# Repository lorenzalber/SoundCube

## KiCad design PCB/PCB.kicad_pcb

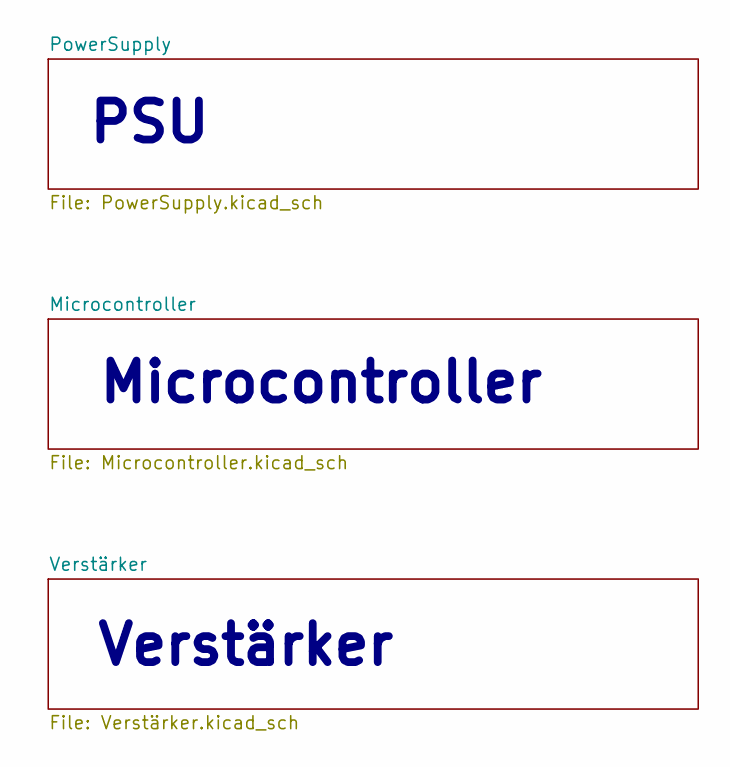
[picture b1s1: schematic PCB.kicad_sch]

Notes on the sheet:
Microcontroller
PSU
Verstärker

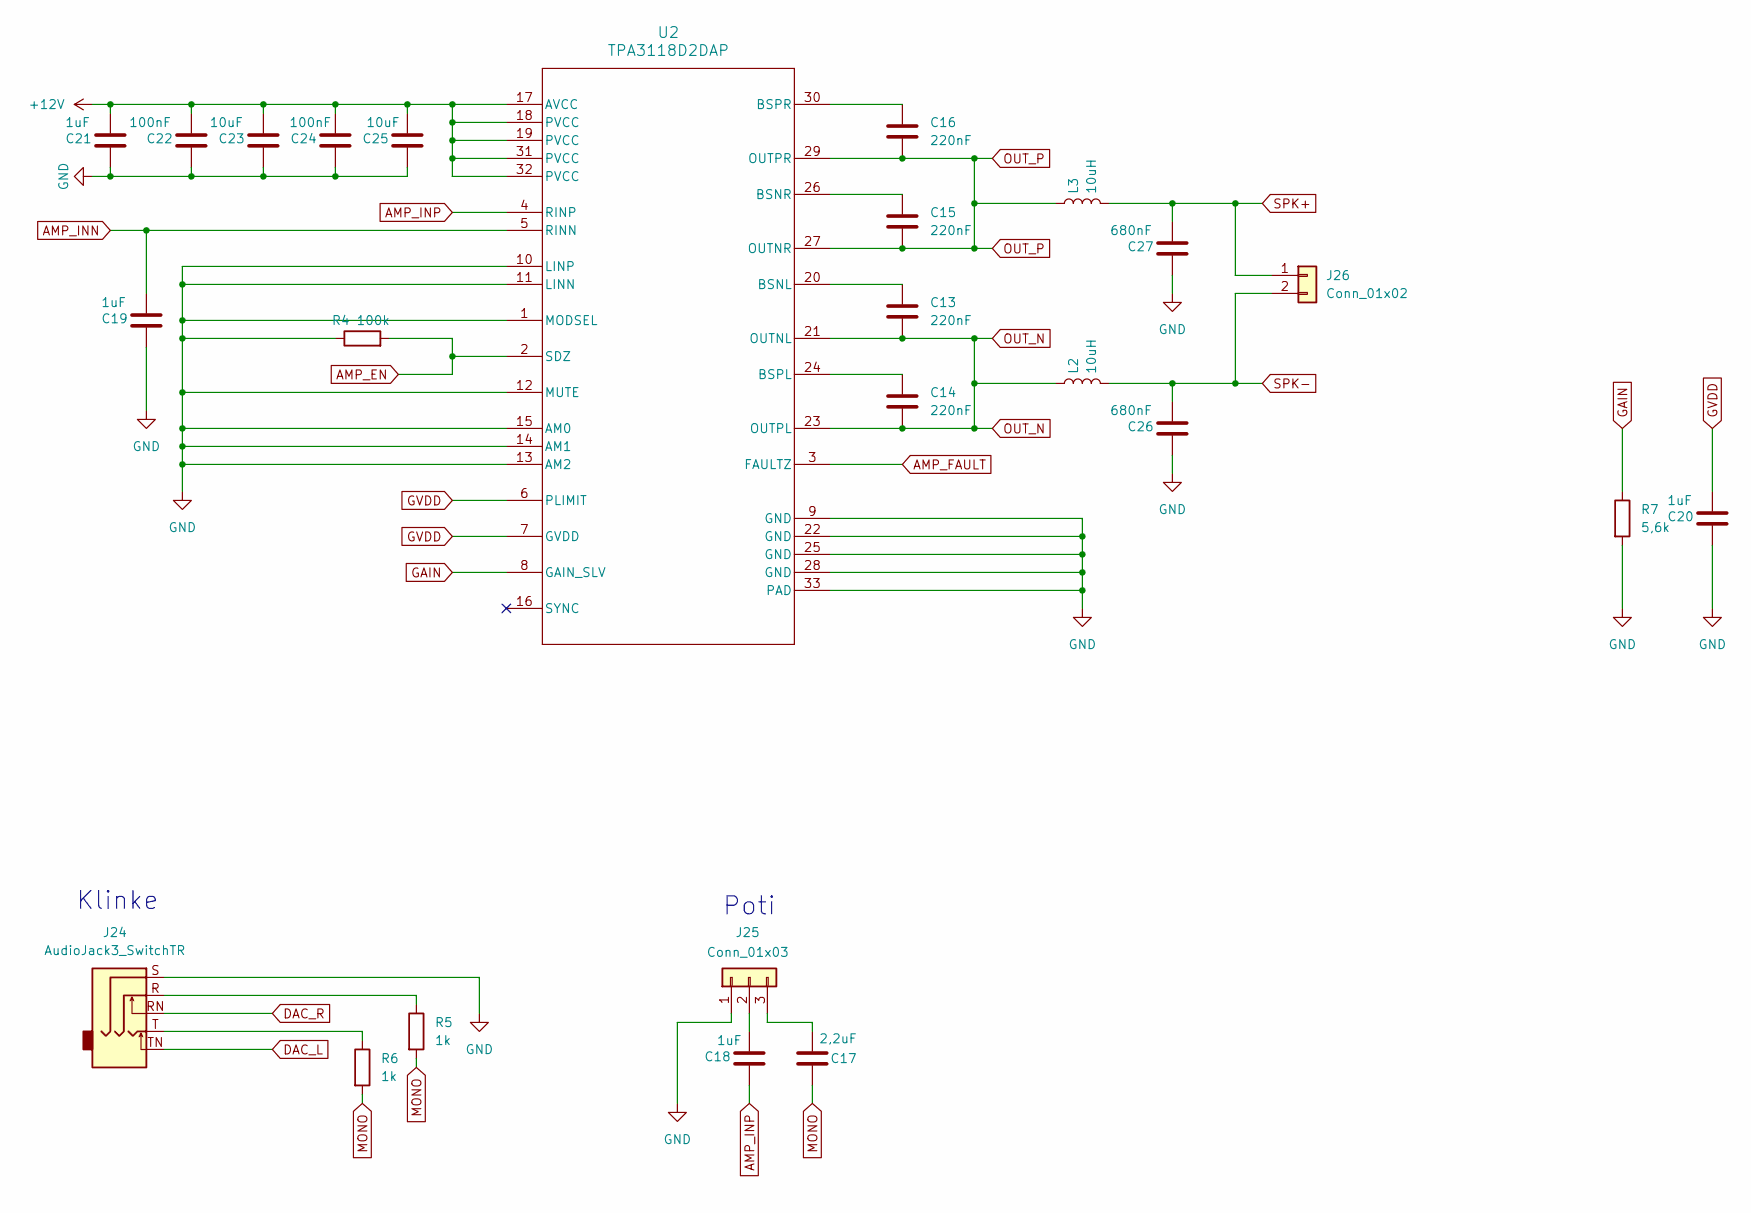
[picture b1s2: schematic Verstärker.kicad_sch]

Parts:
C13, C14, C15, C16: 220nF; C_0805_2012Metric
C17: 2,2uF; C_0805_2012Metric
C18, C19, C20, C21: 1uF; C_0805_2012Metric
C22, C24: 100nF; C_0805_2012Metric
C23, C25: 10uF; C_0805_2012Metric
C26, C27: 680nF; C_Rect_L7.2mm_W5.5mm_P5.00mm_FKS2_FKP2_MKS2_MKP2
J24: AudioJack3_SwitchTR; Jack_3.5mm_CUI_SJ1-3535NG_Horizontal
J25: Conn_01x03; SolderWire-1sqmm_1x03_P5.4mm_D1.4mm_OD2.7mm
J26: Conn_01x02; SolderWire-1sqmm_1x02_P5.4mm_D1.4mm_OD2.7mm
L2, L3: 10uH; L_Bourns_SRR1260
R4: 100k; R_0805_2012Metric
R5, R6: 1k; R_0805_2012Metric
R7: 5,6k; R_0805_2012Metric
U2: TPA3118D2DAP; DAP0032A_M

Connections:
+12V: C21.2, C22.2, C23.2, C24.2, C25.2, U2.17 (AVCC), U2.18 (PVCC), U2.19 (PVCC), U2.31 (PVCC), U2.32 (PVCC); also elsewhere on the board
AMP_EN: R4.2, U2.2 (SDZ); also elsewhere on the board
AMP_FAULT: U2.3 (FAULTZ); also elsewhere on the board
AMP_INN: C19.2, U2.5 (RINN)
AMP_INP: C18.1, U2.4 (RINP)
DAC_L: J24.TN; also elsewhere on the board
DAC_R: J24.RN; also elsewhere on the board
GAIN: R7.1, U2.8 (GAIN_SLV)
GND: C19.1, C20.1, C21.1, C22.1, C23.1, C24.1, C25.1, C26.1, C27.1, J24.S, J25.1, R4.1, R7.2, U2.1 (MODSEL), U2.9 (GND), U2.10 (LINP), U2.11 (LINN), U2.12 (MUTE), U2.13 (AM2), U2.14 (AM1), U2.15 (AM0), U2.22 (GND), U2.25 (GND), U2.28 (GND), U2.33 (PAD); also elsewhere on the board
GVDD: C20.2, U2.6 (PLIMIT), U2.7 (GVDD)
MONO: C17.1, R5.2, R6.2
unnamed: J24.R, R5.1
unnamed: J24.T, R6.1
unnamed: C18.2, J25.2
unnamed: C17.2, J25.3
unnamed: C13.1, U2.20 (BSNL)
unnamed: C15.1, U2.26 (BSNR)
unnamed: C14.1, U2.24 (BSPL)
unnamed: C16.1, U2.30 (BSPR)
OUT_N: C13.2, C14.2, L2.1, U2.21 (OUTNL), U2.23 (OUTPL)
OUT_P: C15.2, C16.2, L3.1, U2.27 (OUTNR), U2.29 (OUTPR)
SPK+: C27.2, J26.1, L3.2
SPK-: C26.2, J26.2, L2.2

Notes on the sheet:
Poti
Klinke

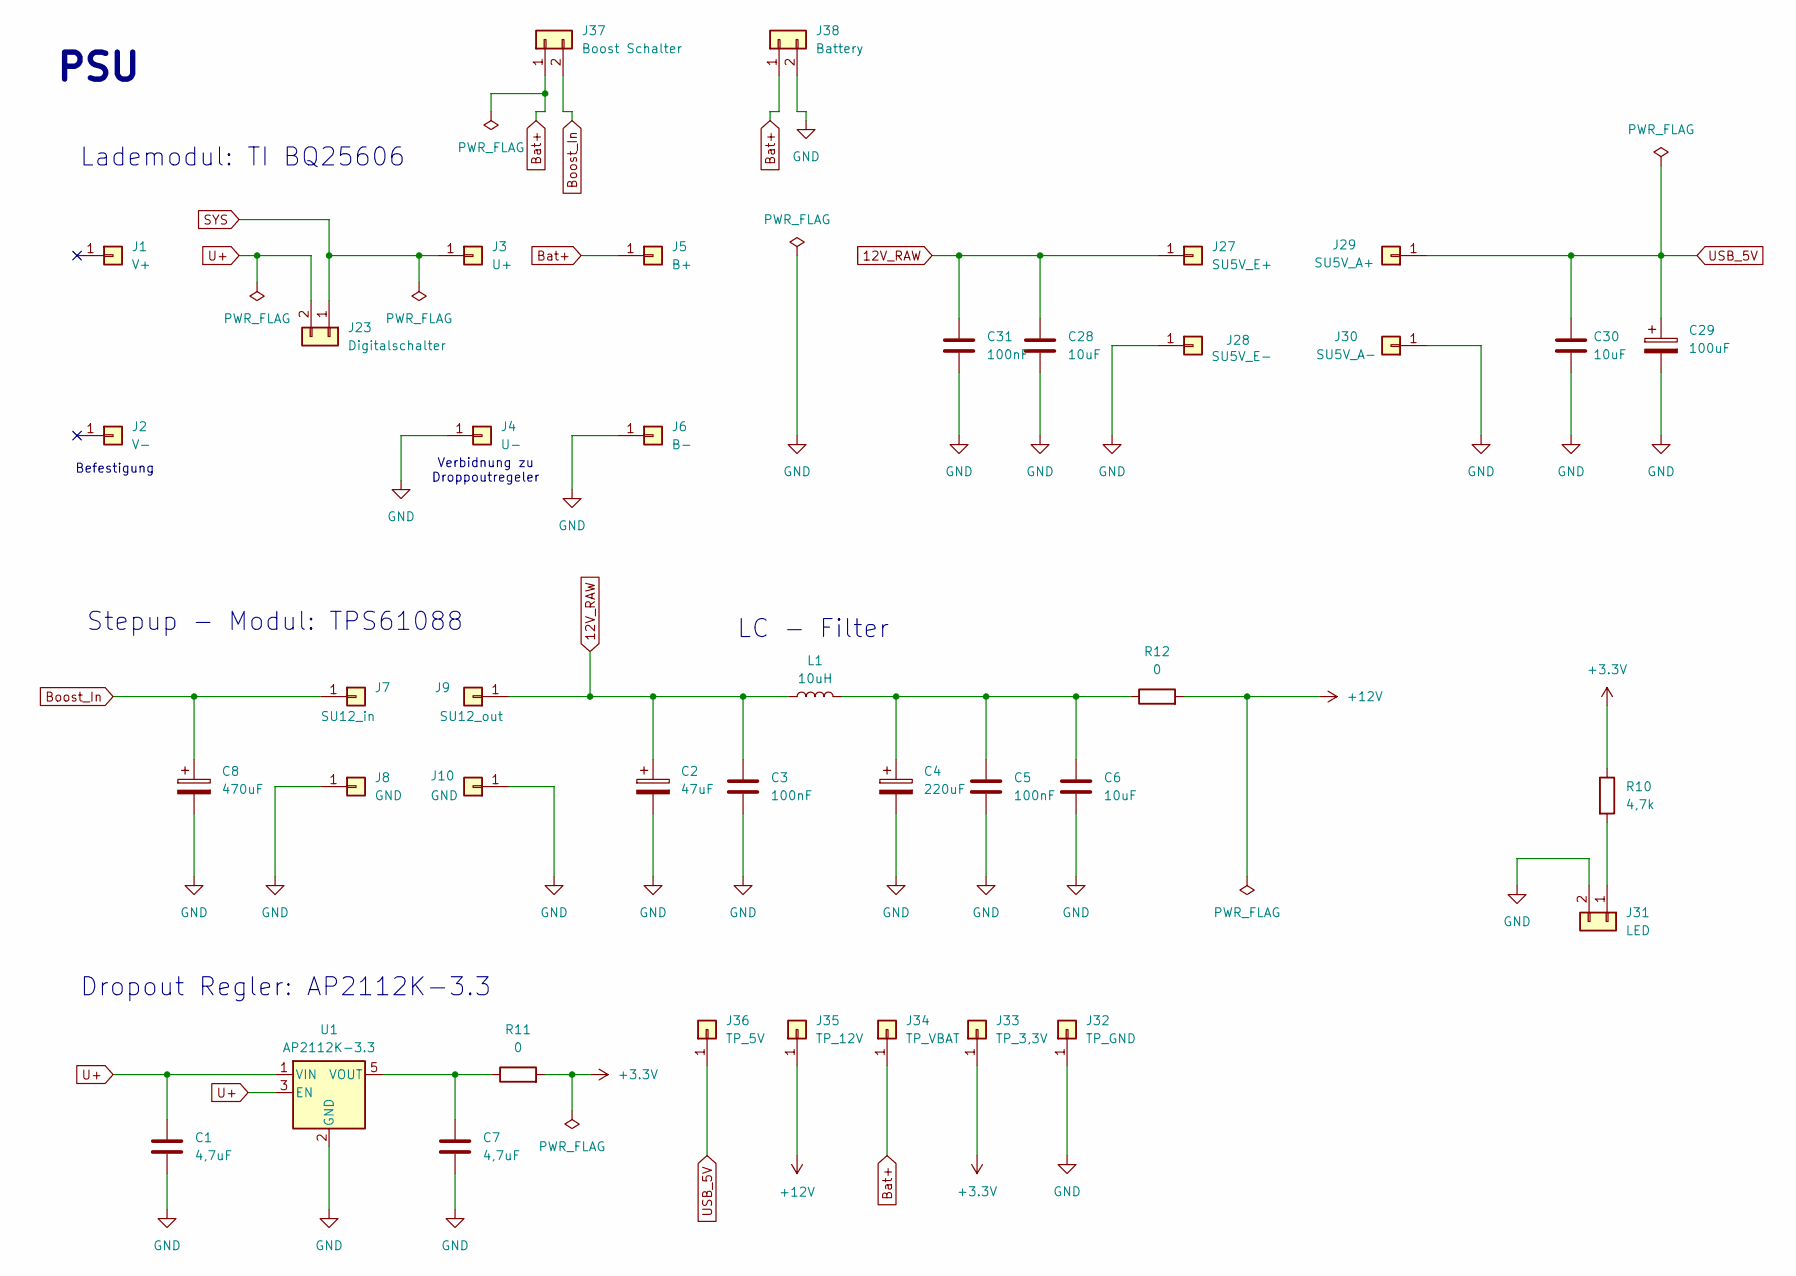
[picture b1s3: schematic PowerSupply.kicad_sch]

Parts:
C1, C7: 4,7uF; C_0805_2012Metric
C2: 47uF; CP_Radial_D6.3mm_P2.50mm
C3, C5, C31: 100nF; C_0805_2012Metric
C4: 220uF; CP_Radial_D8.0mm_P3.50mm
C6, C28, C30: 10uF; C_0805_2012Metric
C8: 470uF; CP_Radial_D8.0mm_P3.50mm
C29: 100uF; CP_Radial_D6.3mm_P2.50mm
J1: V+; PinHeader_1x01_P2.00mm_Vertical
J2: V-; PinHeader_1x01_P2.00mm_Vertical
J3: U+; PinHeader_1x01_P2.00mm_Vertical
J4: U-; PinHeader_1x01_P2.00mm_Vertical
J5: B+; PinHeader_1x01_P2.00mm_Vertical
J6: B-; PinHeader_1x01_P2.00mm_Vertical
J7: SU12_in; SolderWire-1sqmm_1x01_D1.4mm_OD2.7mm
J8, J10: GND; SolderWire-1sqmm_1x01_D1.4mm_OD2.7mm
J9: SU12_out; SolderWire-1sqmm_1x01_D1.4mm_OD2.7mm
J23: Digitalschalter; SolderWire-1sqmm_1x02_P5.4mm_D1.4mm_OD2.7mm
J27: SU5V_E+; PinHeader_1x01_P2.00mm_Vertical
J28: SU5V_E-; PinHeader_1x01_P2.00mm_Vertical
J29: SU5V_A+; PinHeader_1x01_P2.00mm_Vertical
J30: SU5V_A-; PinHeader_1x01_P2.00mm_Vertical
J31: LED; PinHeader_1x02_P2.54mm_Vertical
J32: TP_GND; PinHeader_1x01_P2.00mm_Vertical
J33: TP_3,3V; PinHeader_1x01_P2.00mm_Vertical
J34: TP_VBAT; PinHeader_1x01_P2.00mm_Vertical
J35: TP_12V; PinHeader_1x01_P2.00mm_Vertical
J36: TP_5V; PinHeader_1x01_P2.00mm_Vertical
J37: Boost Schalter; SolderWire-1sqmm_1x02_P5.4mm_D1.4mm_OD2.7mm
J38: Battery; SolderWire-1sqmm_1x02_P5.4mm_D1.4mm_OD2.7mm
L1: 10uH; L_Bourns_SRR1260
R10: 4,7k; R_0603_1608Metric
R11: 0; R_0603_1608Metric
R12: 0; R_Axial_DIN0207_L6.3mm_D2.5mm_P10.16mm_Horizontal
U1: AP2112K-3.3; SOT-23-5_HandSoldering

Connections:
12V_RAW: C2.1, C3.1, C28.1, C31.1, J9.1 (Pin_1_1), J27.1 (Pin_1_1), L1.1
+3.3V: J33.1 (Pin_1_1), R10.1, R11.2; also elsewhere on the board
+12V: J35.1 (Pin_1_1), R12.2; also elsewhere on the board
Bat+: J5.1 (Pin_1_1), J34.1 (Pin_1_1), J37.1, J38.1
Boost_In: C8.1, J7.1 (Pin_1_1), J37.2
GND: C1.2, C2.2, C3.2, C4.2, C5.2, C6.2, C7.2, C8.2, C28.2, C29.2, C30.2, C31.2, J4.1 (Pin_1_1), J6.1 (Pin_1_1), J8.1 (Pin_1_1), J10.1 (Pin_1_1), J28.1 (Pin_1_1), J30.1 (Pin_1_1), J31.2, J32.1 (Pin_1_1), J38.2, U1.2 (GND); also elsewhere on the board
unnamed: C4.1, C5.1, C6.1, L1.2, R12.1
unnamed: J31.1, R10.2
unnamed: C7.1, R11.1, U1.5 (VOUT)
SYS: J3.1 (Pin_1_1), J23.1
U+: C1.1, J23.2, U1.1 (VIN), U1.3 (EN); also elsewhere on the board
USB_5V: C29.1, C30.1, J29.1 (Pin_1_1), J36.1 (Pin_1_1); also elsewhere on the board

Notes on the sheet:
Befestigung
Lademodul: TI BQ25606
Stepup - Modul: TPS61088
Dropout Regler: AP2112K-3.3
LC - Filter
Verbidnung zu Droppoutregeler
PSU

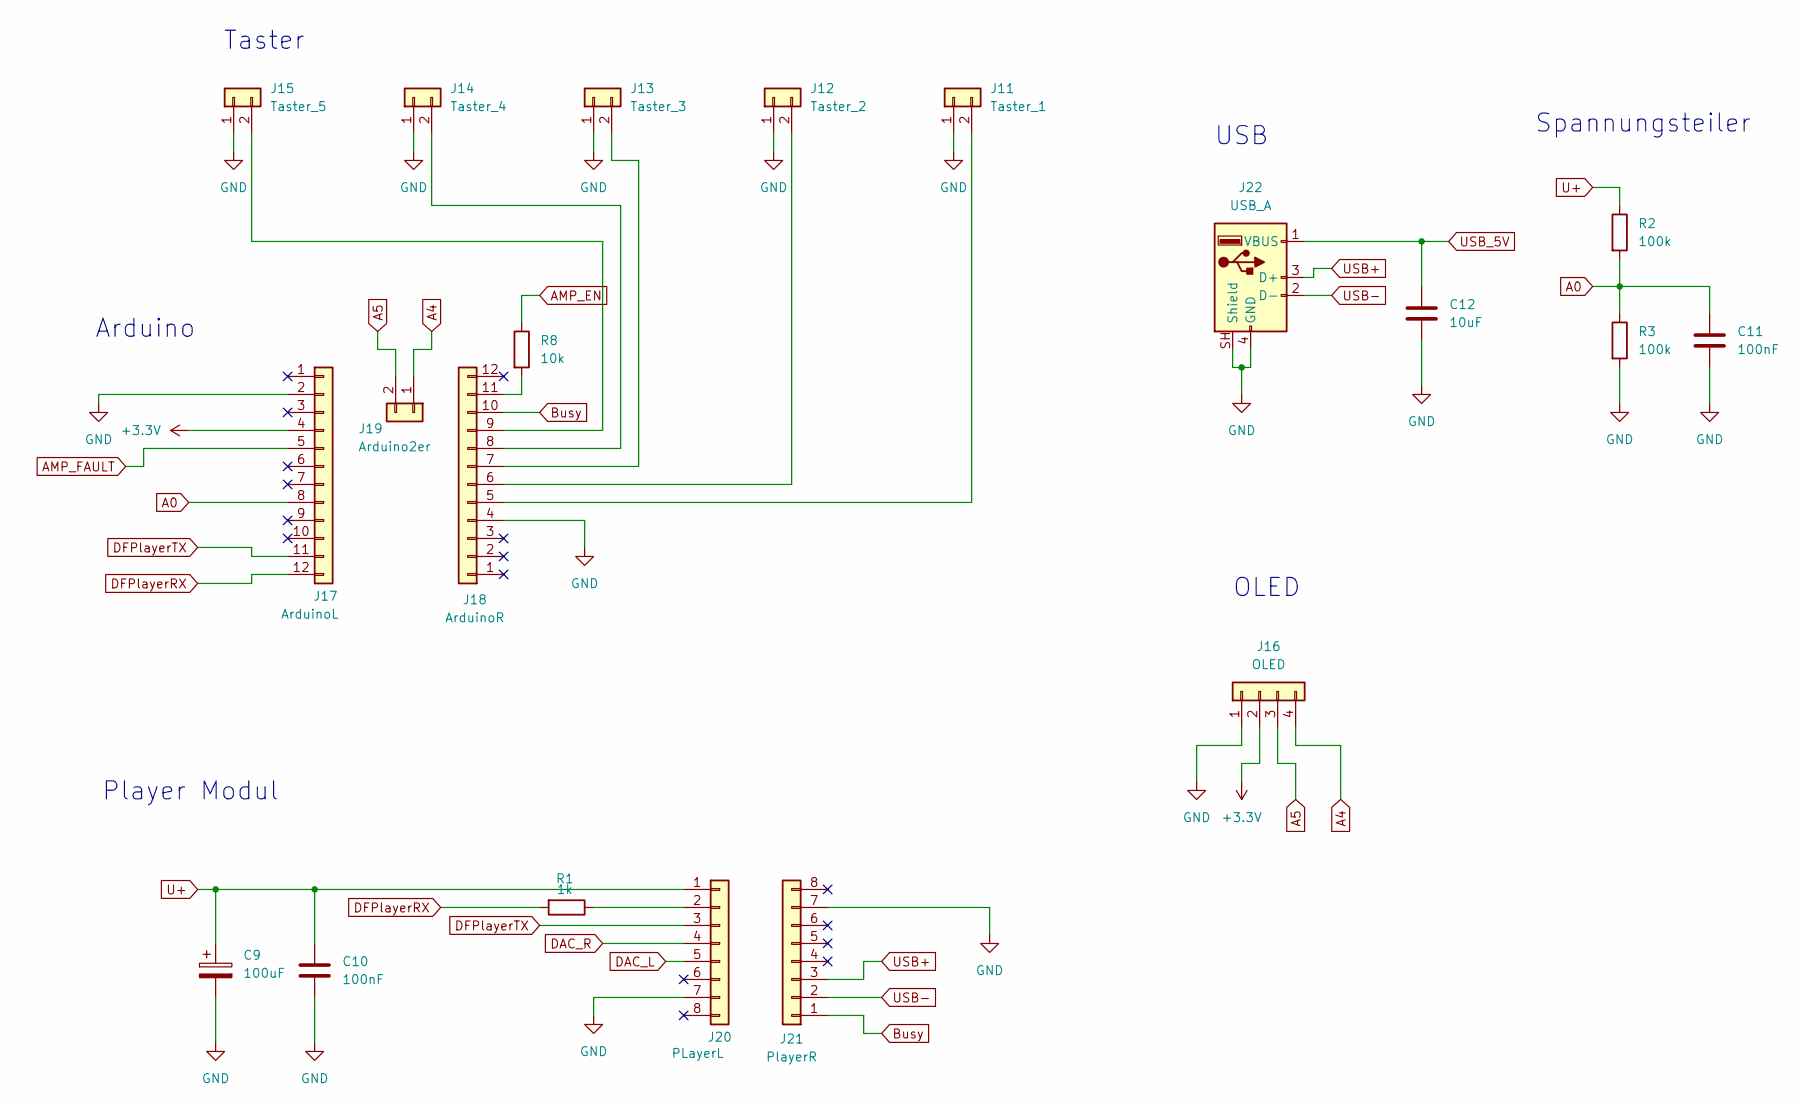
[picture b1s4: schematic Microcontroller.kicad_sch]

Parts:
C9: 100uF; CP_Radial_D6.3mm_P2.50mm
C10, C11: 100nF; C_0805_2012Metric
C12: 10uF; C_0805_2012Metric
J11: Taster_1; PinHeader_1x02_P2.54mm_Vertical
J12: Taster_2; PinHeader_1x02_P2.54mm_Vertical
J13: Taster_3; PinHeader_1x02_P2.54mm_Vertical
J14: Taster_4; PinHeader_1x02_P2.54mm_Vertical
J15: Taster_5; PinHeader_1x02_P2.54mm_Vertical
J16: OLED; PinHeader_1x04_P2.54mm_Vertical
J17: ArduinoL; PinHeader_1x12_P2.54mm_Vertical
J18: ArduinoR; PinHeader_1x12_P2.54mm_Vertical
J19: Arduino2er; PinHeader_1x02_P2.54mm_Vertical
J20: PLayerL; PinHeader_1x08_P2.54mm_Vertical
J21: PlayerR; PinHeader_1x08_P2.54mm_Vertical
J22: USB_A; USB_A_CNCTech_1001-011-01101_Horizontal
R1: 1k; R_0603_1608Metric
R2, R3: 100k; R_0603_1608Metric
R8: 10k; R_0603_1608Metric

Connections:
+3.3V: J16.2, J17.4; also elsewhere on the board
A0: C11.1, J17.8, R2.2, R3.1
A4: J16.4, J19.1
A5: J16.3, J19.2
AMP_EN: R8.1; also elsewhere on the board
AMP_FAULT: J17.5; also elsewhere on the board
Busy: J18.10, J21.1
DAC_L: J20.5; also elsewhere on the board
DAC_R: J20.4; also elsewhere on the board
DFPlayerRX: J17.12, R1.2
DFPlayerTX: J17.11, J20.3
GND: C9.2, C10.2, C11.2, C12.2, J11.1, J12.1, J13.1, J14.1, J15.1, J16.1, J17.2, J18.4, J20.7, J21.7, J22.4 (GND), J22.SH (Shield), R3.2; also elsewhere on the board
unnamed: J11.2, J18.5
unnamed: J12.2, J18.6
unnamed: J13.2, J18.7
unnamed: J14.2, J18.8
unnamed: J15.2, J18.9
unnamed: J18.11, R8.2
unnamed: J20.2, R1.1
U+: C9.1, C10.1, J20.1, R2.1; also elsewhere on the board
USB+: J21.3, J22.3 (D+)
USB-: J21.2, J22.2 (D-)
USB_5V: C12.1, J22.1 (VBUS); also elsewhere on the board

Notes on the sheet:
Arduino
OLED
Taster
Spannungsteiler
Player Modul
USB

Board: 2 copper layers, 85 parts (0 on the bottom side), 48 nets, no tracks yet.
